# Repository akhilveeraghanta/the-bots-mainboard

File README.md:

# The Bots Mainboard

This is my first PCB design project. The majoriy of this board/schematics were created watching [Phils Lab](https://www.youtube.com/@PhilsLab) on youtube and using his projects as examples. 

The soccer playing AI will compute target velocities for all 6 robots and send them over USB to the mainboard, which will then send the velocity data over radio. Each robot will have its own mainboard, receive the pacet over radio, unpack and send a velocity command over the CAN Bus (which is then picked up by the motor controllers)

So the main goal of the board is to act as a radio to CAN bridge if flashed as a robot, and a radio to USB bridge if flashed as a dongle and plugged into the computer running AI.

Additionally, the ball detector circuit, when plugged into a robot will be facing the "mouth" of the robot to detect any balls that enter. This helps with determining when to kick/chip the golf ball.

Here is one of our competitors, UBC Thunderbots's robot to put this board into perspective. (We don't have robots yet)

and more info about robocup can be [found here](https://ssl.robocup.org/)

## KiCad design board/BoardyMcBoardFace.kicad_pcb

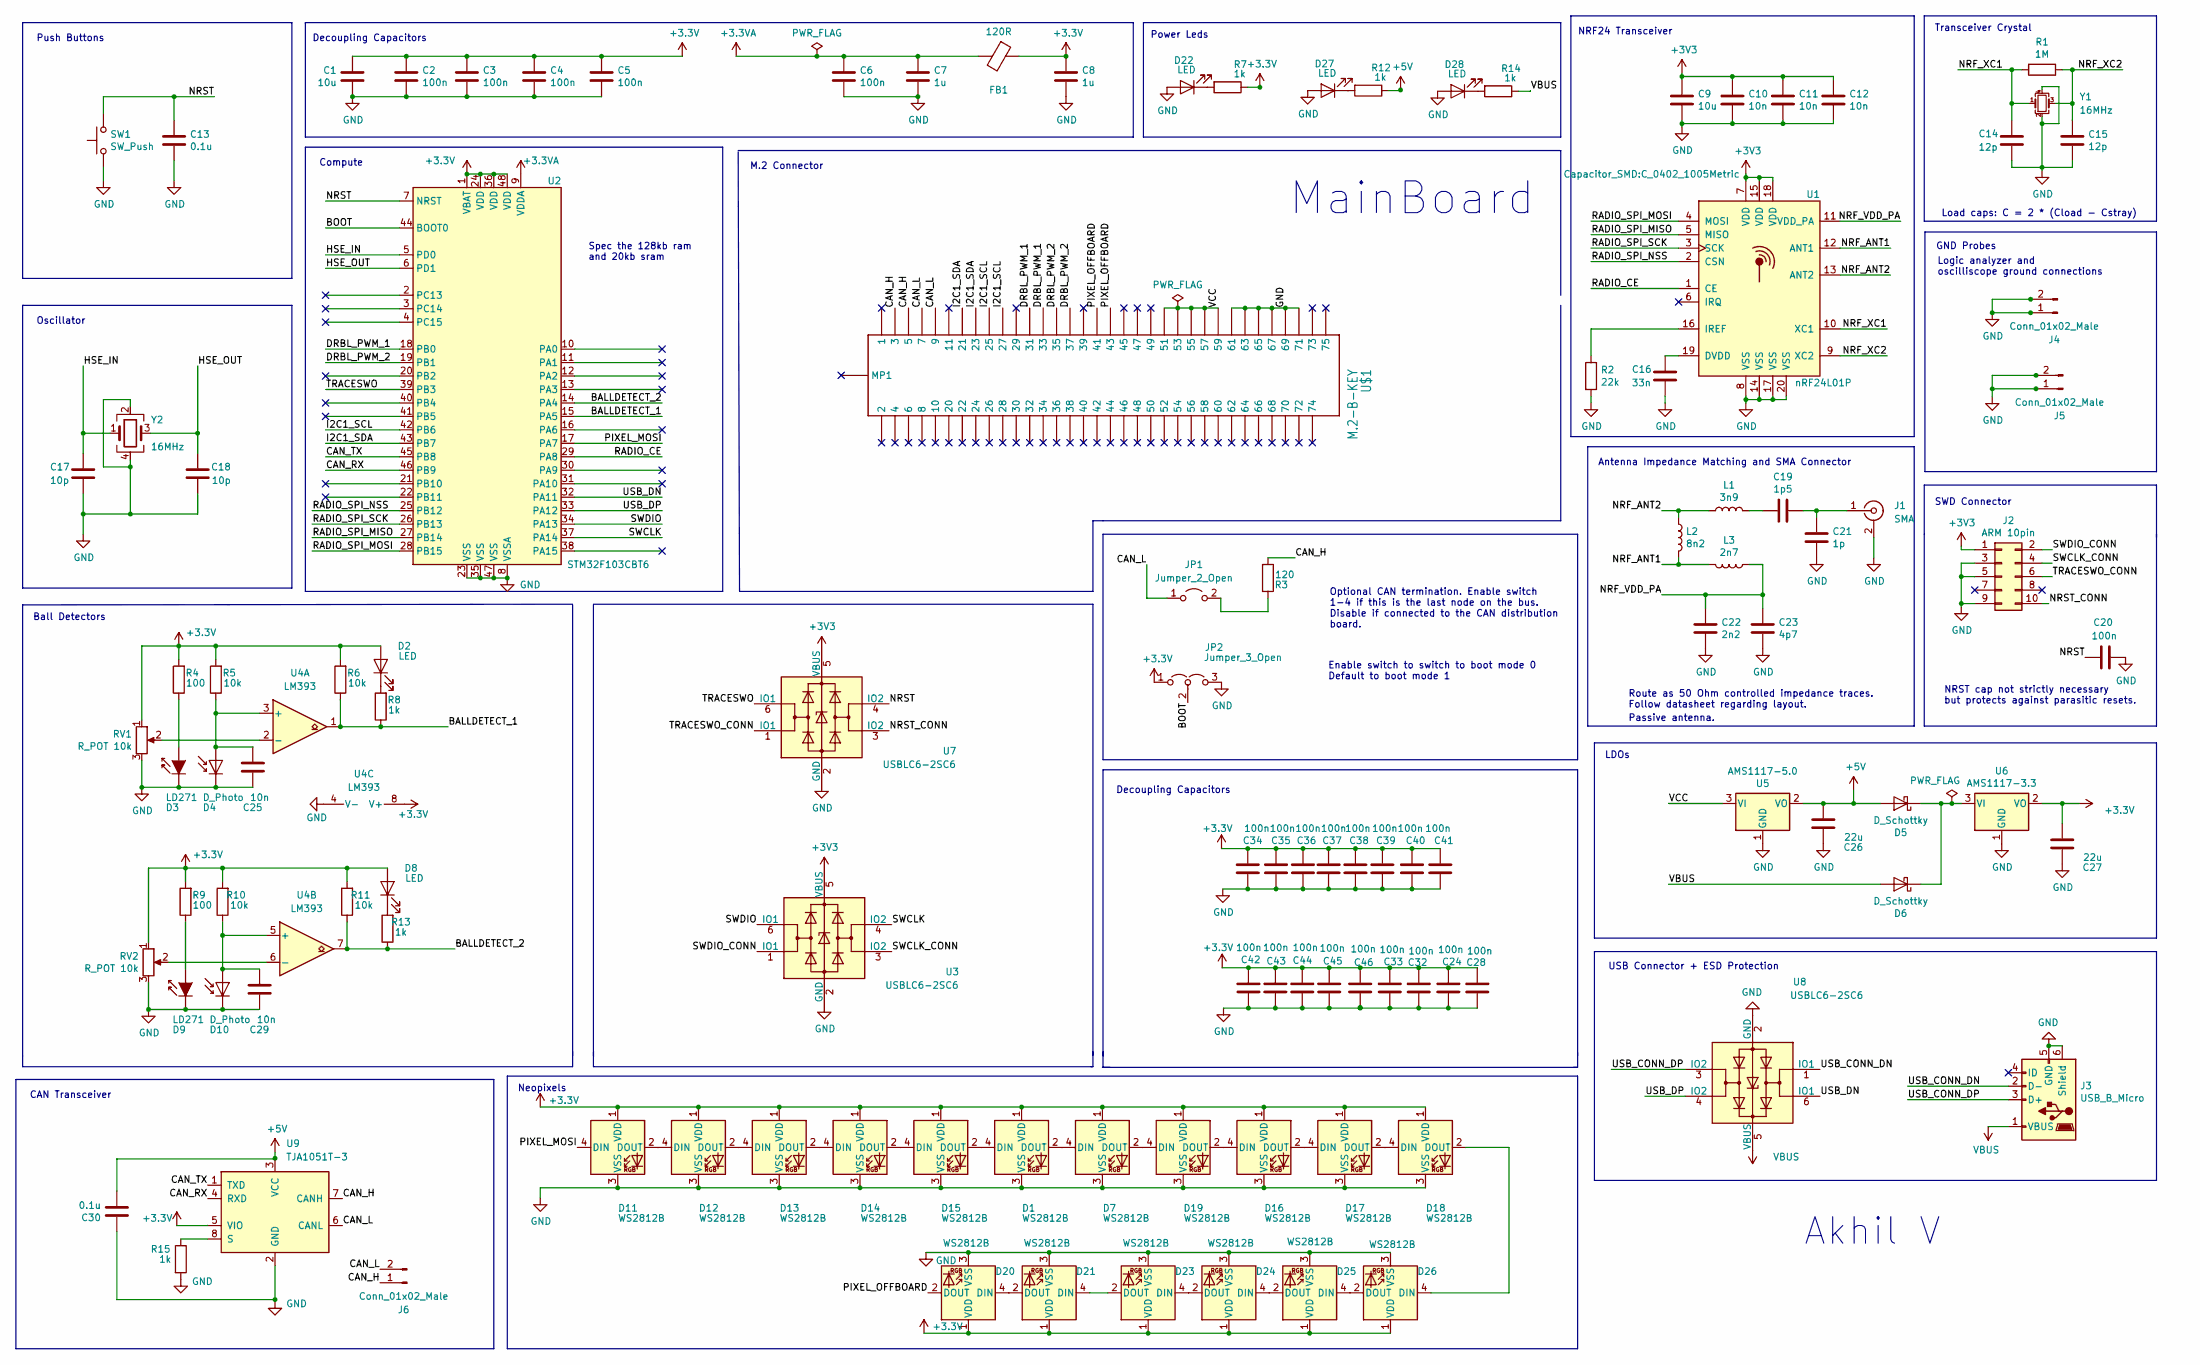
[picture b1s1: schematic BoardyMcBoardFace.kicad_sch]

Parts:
C1, C9: 10u; C_0402_1005Metric
C2, C3, C4, C5, C6, C20, C24, C28, C32, C33, C34, C35, C36, C37, C38, C39, C40, C41, C42, C43, C44, C45, C46: 100n; C_0402_1005Metric
C7, C8: 1u; C_0402_1005Metric
C10, C11, C12, C25, C29: 10n; C_0402_1005Metric
C13, C30: 0.1u; C_0402_1005Metric
C14, C15: 12p; C_0402_1005Metric
C16: 33n; C_0402_1005Metric
C17, C18: 10p; C_0402_1005Metric
C19: 1p5; C_0402_1005Metric
C21: 1p; C_0402_1005Metric
C22: 2n2; C_0402_1005Metric
C23: 4p7; C_0402_1005Metric
C26: 22u; C_0402_1005Metric
C27: 22u; C_0805_2012Metric
D1, D7, D11, D12, D13, D14, D15, D16, D17, D18, D19, D20, D21, D23, D24, D25, D26: WS2812B; LED_WS2812B-2020_PLCC4_2.0x2.0mm
D2, D8, D22, D27, D28: LED; LED_0402_1005Metric
D3, D9: LD271; LED_D5.0mm_IRGrey
D4, D10: D_Photo; LED_D5.0mm_IRGrey
D5, D6: D_Schottky; D_0805_2012Metric
FB1: 120R; L_0805_2012Metric
J1: SMA; SMA_Samtec_SMA-J-P-X-ST-EM1_EdgeMount
J2: ARM 10pin; PinHeader_2x05_P1.27mm_Vertical
J3: USB_B_Micro; USB_Micro-B_Molex_47346-0001
J4, J5, J6: Conn_01x02_Male; PinHeader_1x02_P1.27mm_Vertical
JP1: Jumper_2_Open; PinHeader_1x02_P1.27mm_Vertical
JP2: Jumper_3_Open; PinHeader_1x03_P1.27mm_Vertical
L1: 3n9; L_0402_1005Metric
L2: 8n2; L_0402_1005Metric
L3: 2n7; L_0402_1005Metric
R1: 1M; R_0402_1005Metric
R2: 22k; R_0402_1005Metric
R3: 120; R_0402_1005Metric
R4, R9: 100; R_0402_1005Metric
R5, R6, R10, R11: 10k; R_0402_1005Metric
R7, R8, R12, R13, R14, R15: 1k; R_0402_1005Metric
RV1, RV2: R_POT 10k; Potentiometer_Bourns_3266X_Horizontal
SW1: SW_Push; TS-1187A-B-A-B
U1: nRF24L01P; QFN-20-1EP_4x4mm_P0.5mm_EP2.5x2.5mm
U2: STM32F103CBT6; LQFP-48_7x7mm_P0.5mm
U3, U7, U8: USBLC6-2SC6; SOT-23-6
U4: LM393; SOIC-8_3.9x4.9mm_P1.27mm
U5: AMS1117-5.0; SOT-223-3_TabPin2
U6: AMS1117-3.3; SOT-223-3_TabPin2
U9: TJA1051T-3; SOIC-8_3.9x4.9mm_P1.27mm
U$1: M.2-B-KEY
Y1, Y2: 16MHz; Crystal_SMD_3225-4Pin_3.2x2.5mm

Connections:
+3.3VA: C6.1, C7.1, FB1.2, U2.9 (VDDA)
+5V: C26.2, C30.2, D5.2 (A), R12.1, U5.2 (VO), U9.3 (VCC)
/BALLDETECT_1: R6.1, R8.1, U2.15 (PA5), U4.1
/BALLDETECT_2: R11.1, R13.1, U2.14 (PA4), U4.7
/BOOT: JP2.2 (C), U2.44 (BOOT0)
/CAN_H: J6.1, R3.1, U9.7 (CANH), U$1.P$3 (3), U$1.P$5 (5)
/CAN_L: J6.2, JP1.1 (A), U9.6 (CANL), U$1.P$7 (7), U$1.P$9 (9)
/CAN_RX: U2.46 (PB9), U9.4 (RXD)
/CAN_TX: U2.45 (PB8), U9.1 (TXD)
/DRBL_PWM_1: U2.18 (PB0), U$1.P$31 (31), U$1.P$33 (33)
/DRBL_PWM_2: U2.19 (PB1), U$1.P$35 (35), U$1.P$37 (37)
/HSE_IN: C17.1, U2.5 (PD0), Y2.1
/HSE_OUT: C18.1, U2.6 (PD1), Y2.3
/I2C1_SCL: U2.42 (PB6), U$1.P$25 (25), U$1.P$27 (27)
/I2C1_SDA: U2.43 (PB7), U$1.P$21 (21), U$1.P$23 (23)
/NRF_ANT1: L2.2, L3.2, U1.12 (ANT1)
/NRF_ANT2: L1.1, L2.1, U1.13 (ANT2)
/NRF_VDD_PA: C22.2, C23.2, L3.1, U1.11 (VDD_PA)
/NRF_XC1: C14.1, R1.2, U1.10 (XC1), Y1.1
/NRF_XC2: C15.1, R1.1, U1.9 (XC2), Y1.3
/NRST: C13.1, C20.1, SW1.2, U2.7 (NRST), U7.4 (IO2)
/NRST_CONN: J2.10, U7.3 (IO2)
/PIXEL_MOSI: D11.4 (DIN), U2.17 (PA7)
/PIXEL_OFFBOARD: D20.2 (DOUT), U$1.P$41 (41), U$1.P$43 (43)
/RADIO_CE: U1.1 (CE), U2.29 (PA8)
/RADIO_SPI_MISO: U1.5 (MISO), U2.27 (PB14)
/RADIO_SPI_MOSI: U1.4 (MOSI), U2.28 (PB15)
/RADIO_SPI_NSS: U1.2 (CSN), U2.25 (PB12)
/RADIO_SPI_SCK: U1.3 (SCK), U2.26 (PB13)
/SWCLK: U2.37 (PA14), U3.4 (IO2)
/SWCLK_CONN: J2.4, U3.3 (IO2)
/SWDIO: U2.34 (PA13), U3.6 (IO1)
/SWDIO_CONN: J2.2, U3.1 (IO1)
/TRACESWO: U2.39 (PB3), U7.6 (IO1)
/TRACESWO_CONN: J2.6, U7.1 (IO1)
/USB_CONN_DN: J3.2 (D-), U8.1 (IO1)
/USB_CONN_DP: J3.3 (D+), U8.3 (IO2)
/USB_DN: U2.32 (PA11), U8.6 (IO1)
/USB_DP: U2.33 (PA12), U8.4 (IO2)
/VCC: U5.3 (VI), U$1.P$51 (51), U$1.P$53 (53), U$1.P$55 (55), U$1.P$57 (57), U$1.P$59 (59)
GND: C1.2, C2.2, C3.2, C4.2, C5.2, C6.2, C7.2, C8.2, C9.2, C10.2, C11.2, C12.2, C13.2, C14.2, C15.2, C16.2, C17.2, C18.2, C20.2, C21.1, C22.1, C23.1, C24.2, C25.2, C26.1, C27.1, C28.2, C29.2, C30.1, C32.2, C33.2, C34.2, C35.2, C36.2, C37.2, C38.2, C39.2, C40.2, C41.2, C42.2, C43.2, C44.2, C45.2, C46.2, D1.3 (VSS), D3.1 (K), D4.1 (K), D7.3 (VSS), D9.1 (K), D10.1 (K), D11.3 (VSS), D12.3 (VSS), D13.3 (VSS), D14.3 (VSS), D15.3 (VSS), D16.3 (VSS), D17.3 (VSS), D18.3 (VSS), D19.3 (VSS), D20.3 (VSS), D21.3 (VSS), D22.2 (A), D23.3 (VSS), D24.3 (VSS), D25.3 (VSS), D26.3 (VSS), D27.2 (A), D28.2 (A), J1.2 (Ext), J2.3, J2.5, J2.9, J3.5 (GND), J3.6 (Shield), J4.1, J4.2, J5.1, J5.2, JP2.3 (B), R2.2, R15.2, RV1.3, RV2.3, SW1.1, U1.8 (VSS), U1.14 (VSS), U1.17 (VSS), U1.20 (VSS), U2.8 (VSSA), U2.23 (VSS), U2.35 (VSS), U2.47 (VSS), U3.2 (GND), U4.4 (V-), U5.1 (GND), U6.1 (GND), U7.2 (GND), U8.2 (GND), U9.2 (GND), U$1.P$61 (61), U$1.P$63 (63), U$1.P$65 (65), U$1.P$67 (67), U$1.P$69 (69), U$1.P$71 (71), Y1.2, Y1.4, Y2.2, Y2.4
unnamed: C16.1, U1.19 (DVDD)
unnamed: C19.1, C21.2, J1.1 (In)
unnamed: C19.2, L1.2
unnamed: C25.1, D4.2 (A), R5.1, U4.3 (+)
unnamed: C29.1, D10.2 (A), R10.1, U4.5 (+)
unnamed: D1.2 (DOUT), D7.4 (DIN)
unnamed: D1.4 (DIN), D15.2 (DOUT)
unnamed: D2.1 (K), R8.2
unnamed: D3.2 (A), R4.1
unnamed: D5.1 (K), D6.1 (K), U6.3 (VI)
unnamed: D8.1 (K), R13.2
unnamed: D9.2 (A), R9.1
unnamed: D11.2 (DOUT), D12.4 (DIN)
unnamed: D12.2 (DOUT), D13.4 (DIN)
unnamed: D13.2 (DOUT), D14.4 (DIN)
unnamed: D14.2 (DOUT), D15.4 (DIN)
unnamed: D16.2 (DOUT), D17.4 (DIN)
unnamed: D16.4 (DIN), D19.2 (DOUT)
unnamed: D17.2 (DOUT), D18.4 (DIN)
unnamed: D18.2 (DOUT), D26.4 (DIN)
unnamed: D7.2 (DOUT), D19.4 (DIN)
unnamed: D20.4 (DIN), D21.2 (DOUT)
unnamed: D21.4 (DIN), D23.2 (DOUT)
unnamed: D22.1 (K), R7.2
unnamed: D23.4 (DIN), D24.2 (DOUT)
unnamed: D24.4 (DIN), D25.2 (DOUT)
unnamed: D25.4 (DIN), D26.2 (DOUT)
unnamed: D27.1 (K), R12.2
unnamed: D28.1 (K), R14.2
unnamed: JP1.2 (B), R3.2
unnamed: R2.1, U1.16 (IREF)
unnamed: R15.1, U9.8 (S)
unnamed: RV1.2, U4.2 (-)
unnamed: RV2.2, U4.6 (-)
VBUS: D6.2 (A), J3.1 (VBUS), R14.1, U8.5 (VBUS)

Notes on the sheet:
Load caps: C = 2 * (Cload - Cstray)
USB Connector + ESD Protection
Logic analyzer and oscilliscope ground connections
Spec the 128kb ram and 20kb sram
Push Buttons
NRST cap not strictly necessary but protects against parasitic resets.
Route as 50 Ohm controlled impedance traces. Follow datasheet regarding layout.
LDOs
Transceiver Crystal
Decoupling Capacitors
MainBoard
Antenna Impedance Matching and SMA Connector
Optional CAN termination. Enable switch 1-4 if this is the last node on the bus. Disable if connected to the CAN distribution board.
M.2 Connector
GND Probes
CAN Transceiver
Enable switch to switch to boot mode 0 Default to boot mode 1
Power Leds
Neopixels
Akhil V
Oscillator
Ball Detectors
Decoupling Capacitors
NRF24 Transceiver
Compute
SWD Connector
Passive antenna.

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
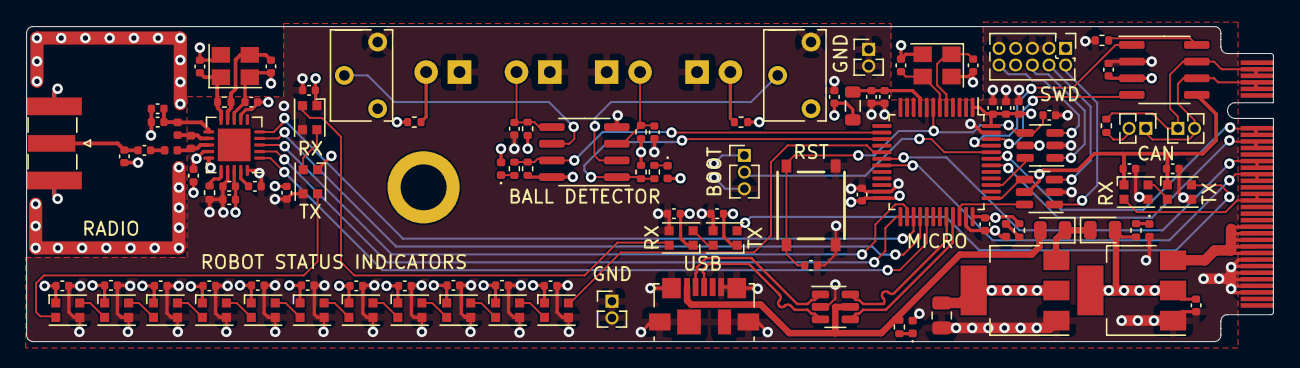
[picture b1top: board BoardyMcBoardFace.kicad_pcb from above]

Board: 4 copper layers, 95.0 x 24.0 mm, 115 parts (0 on the bottom side), 77 nets.

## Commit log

2023-01-03 move from private repo
2023-01-03 move files
2023-01-03 put readme back
2023-01-04 move stuff aroud
2023-01-05 final touches
2023-01-17 finalized
